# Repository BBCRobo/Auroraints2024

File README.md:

Here is a repository of all our hardware (structural) parts, this only includes unique parts

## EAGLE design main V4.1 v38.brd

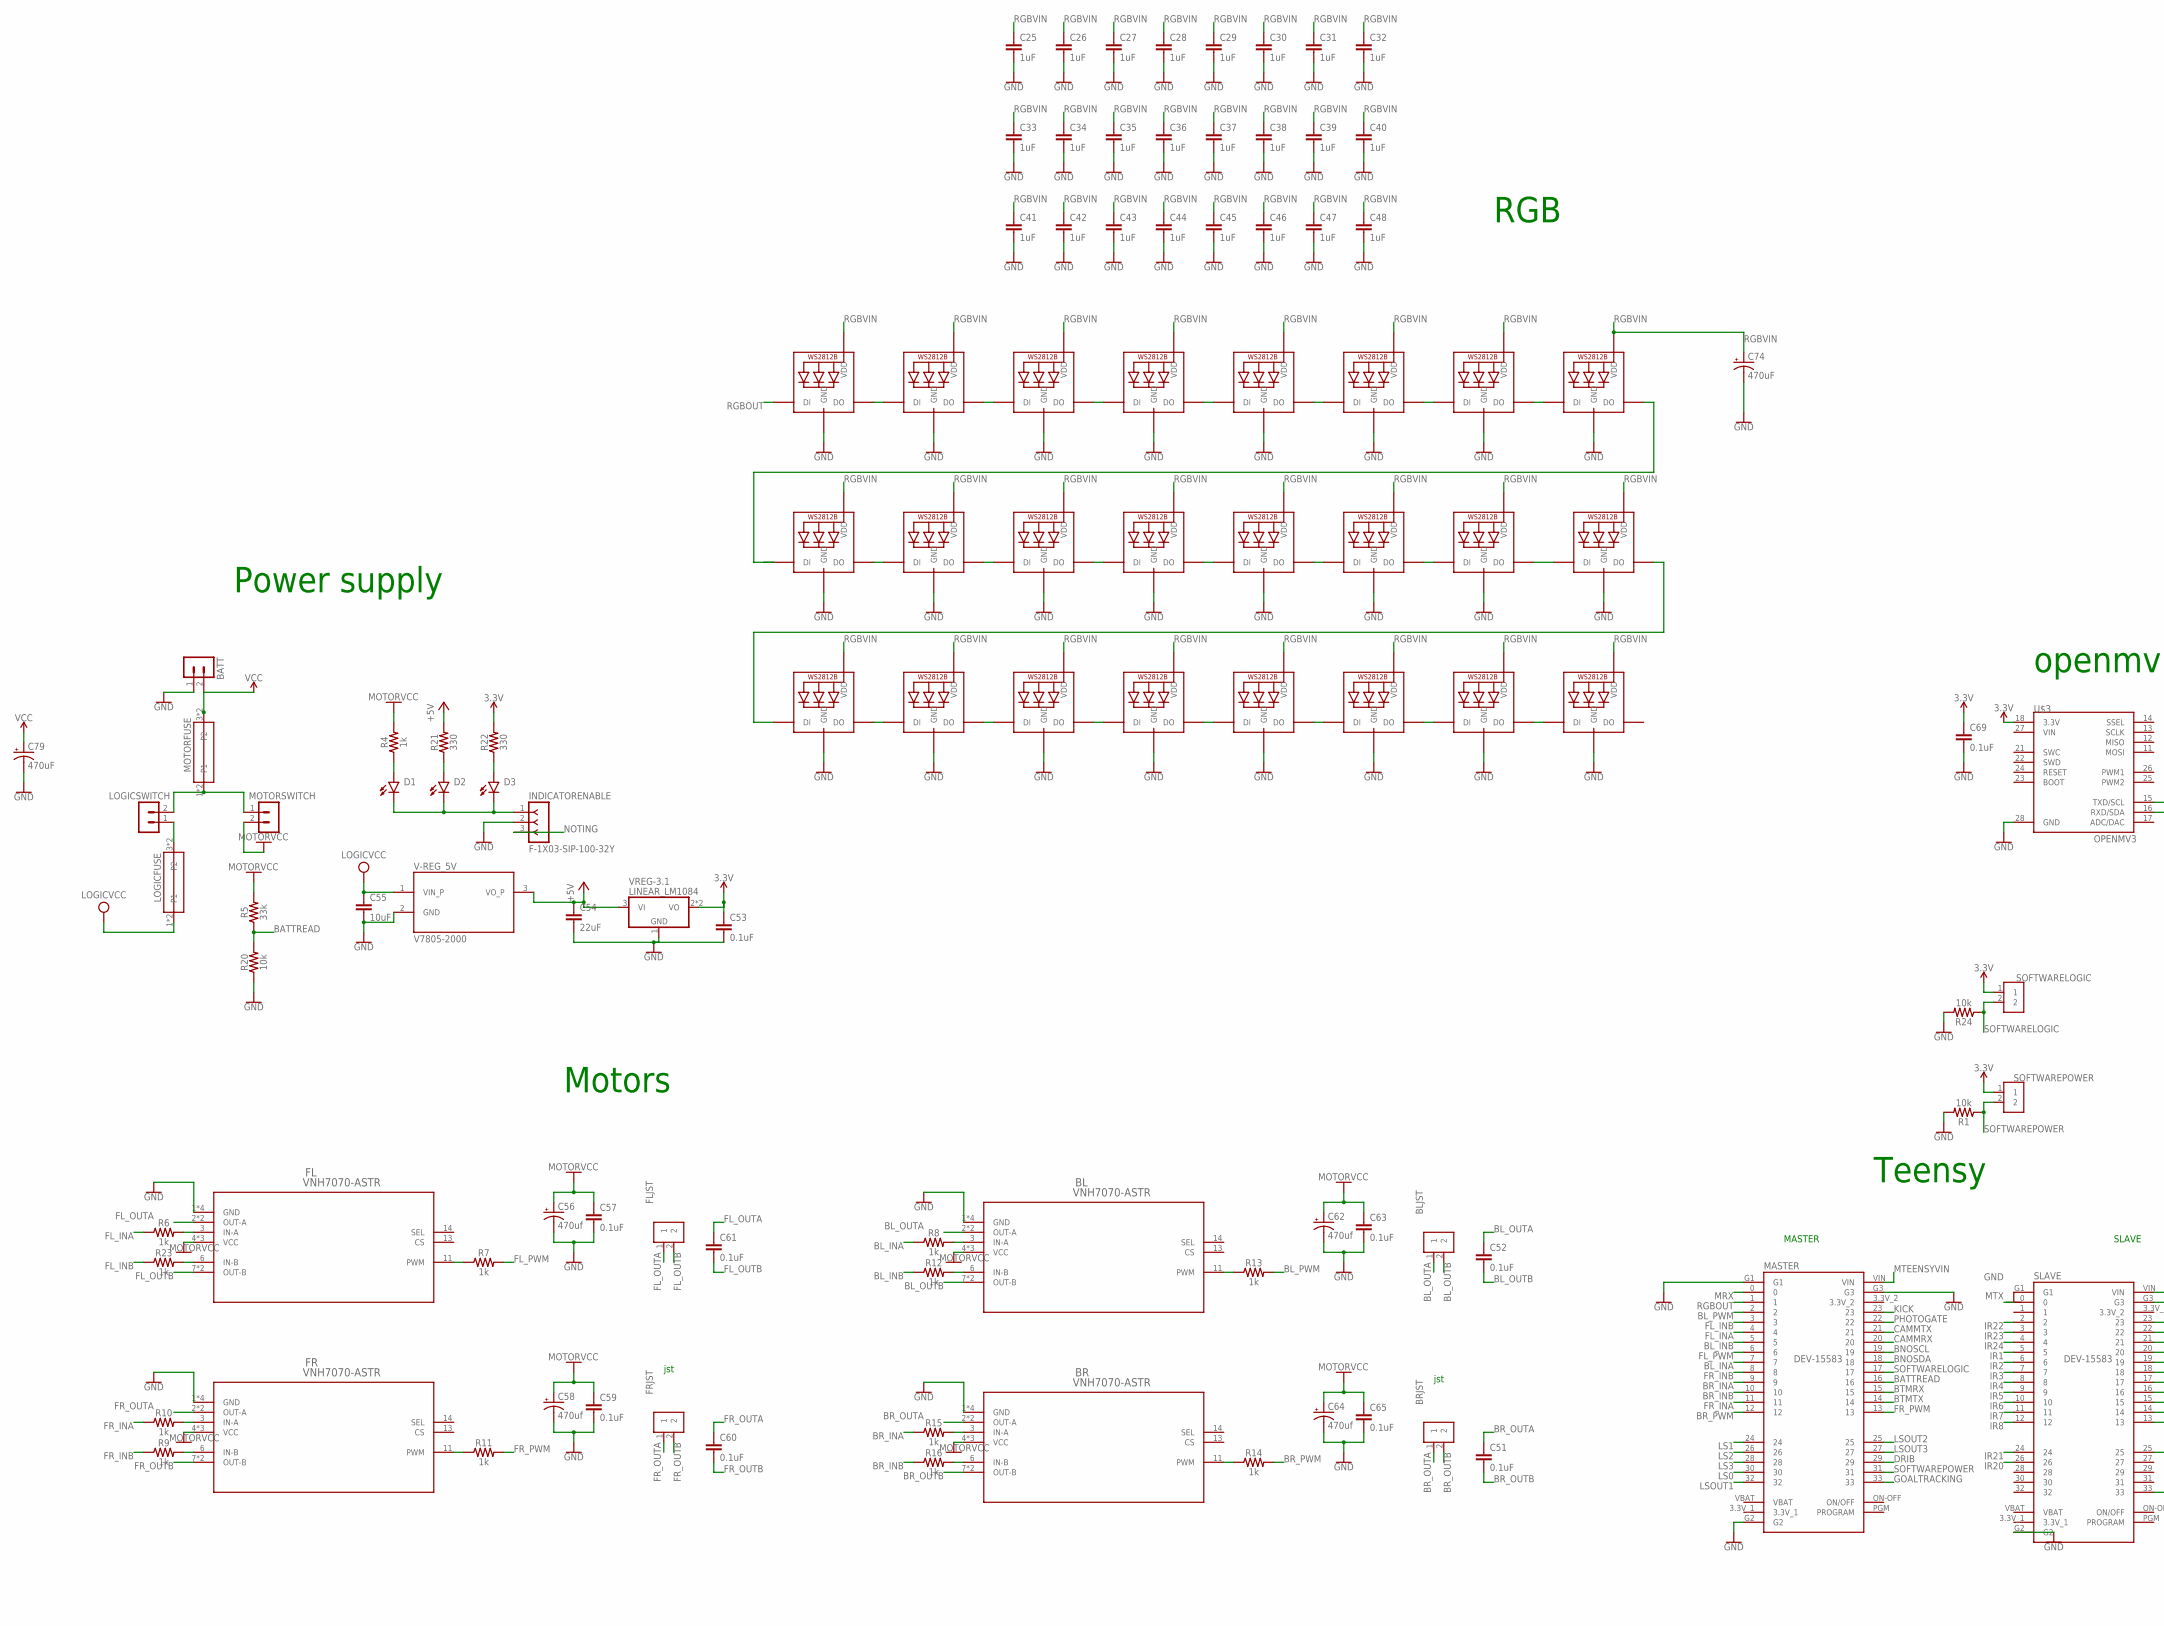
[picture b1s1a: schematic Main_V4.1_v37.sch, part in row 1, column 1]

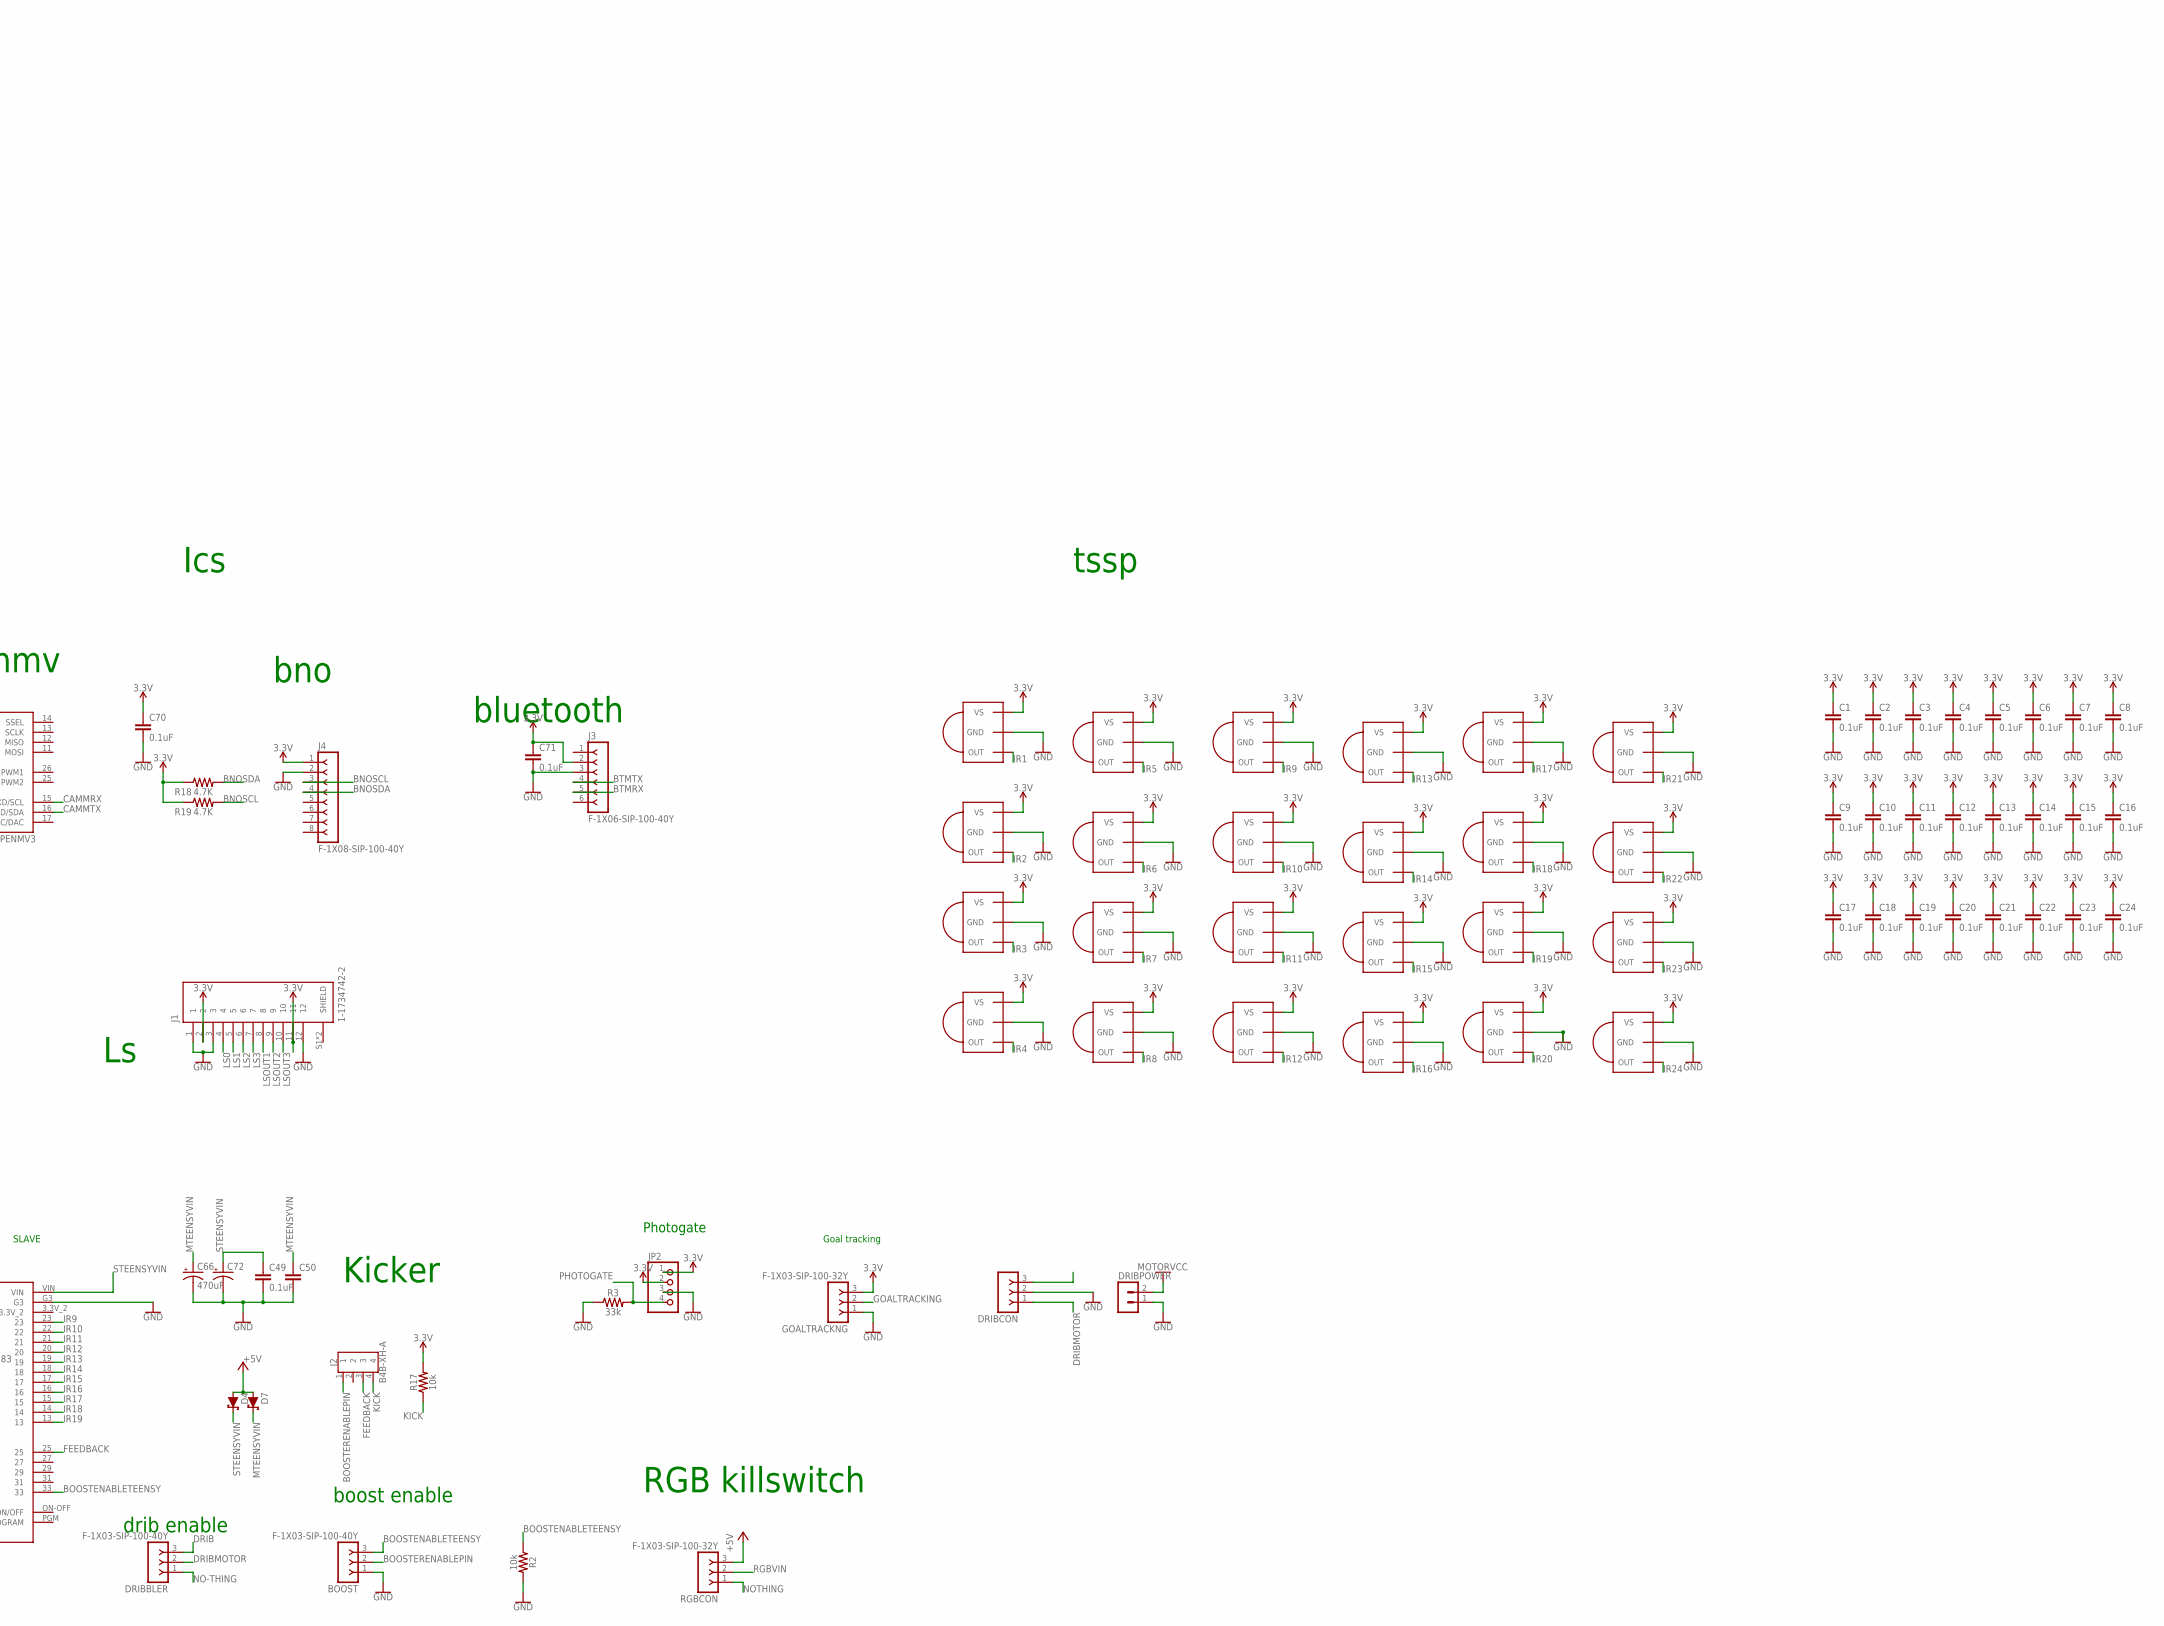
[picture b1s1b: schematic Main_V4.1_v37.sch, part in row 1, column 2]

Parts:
BATT: B2P-VH-B; B2P-VH
BL: VNH7070-ASTR
BLJST: B2B-XH-A
BOOST: F-1X03-SIP-100-40Y; SIP-100-03-40Y
BR: VNH7070-ASTR
BRJST: B2B-XH-A
C1, C2, C3, C4, C5, C6, C7, C8, C9, C10, C11, C12, C13, C14, C15, C16, C17, C18, C19, C20, C21, C22, C23, C24, C49, C50, C51, C52, C53, C57, C59, C60, C61, C63, C65, C69, C70, C71: 0.1uF; 0603
C25, C26, C27, C28, C29, C30, C31, C32, C33, C34, C35, C36, C37, C38, C39, C40, C41, C42, C43, C44, C45, C46, C47, C48: 1uF; 0603
C54: 22uF; 0603
C55: 10uF; 0603
C56, C58, C62, C64: 470uf; CPOL-RADIAL-5MM-10MM-KIT
C66, C72, C74, C79: 470uF; CPOL-RADIAL-5MM-10MM-KIT
D1, D2, D3: CHIP-FLAT-Y_0603-0.55MM; LEDC1608X55N_FLAT-Y
D4, D7: 1A/40V/500mV; SMA-DIODE
DRIBBLER: F-1X03-SIP-100-40Y; SIP-100-03-40Y
DRIBCON: F-1X03-SIP-100-32Y; SIP-100-03-32Y
DRIBPOWER: B2P-VH-B; B2P-VH
FL: VNH7070-ASTR
FLJST: B2B-XH-A
FR: VNH7070-ASTR
FRJST: B2B-XH-A
GOALTRACKNG: F-1X03-SIP-100-32Y; SIP-100-03-32Y
INDICATORENABLE: F-1X03-SIP-100-32Y; SIP-100-03-32Y
IR1, IR2, IR3, IR4, IR5, IR6, IR7, IR8, IR9, IR10, IR11, IR12, IR13, IR14, IR15, IR16, IR17, IR18, IR19, IR20, IR21, IR22, IR23, IR24: TSSP58038; MINICAST
J1: 1-1734742-2; TE_1-1734742-2
J2: B4B-XH-A
J3: F-1X06-SIP-100-40Y; SIP-100-06-40Y
J4: F-1X08-SIP-100-40Y; SIP-100-08-40Y
JP2: PINHD-1X4; 1X04
LED1, LED2, LED3, LED4, LED5, LED6, LED7, LED8, LED9, LED10, LED11, LED12, LED13, LED14, LED15, LED16, LED17, LED18, LED19, LED20, LED21, LED22, LED23, LED24: WS2812B_5050N; WS2812B-NARROW
LOGICFUSE: 3568-FUSEHOLDER
LOGICSWITCH: B2P-VH-B; B2P-VH
MASTER: DEV-15583; MODULE_DEV-15583
MOTORFUSE: 3568-FUSEHOLDER
MOTORSWITCH: B2P-VH-B; B2P-VH
R1, R2, R17, R20, R24: 10k; 0603
R3, R5: 33k; 0603
R4, R6, R7, R8, R9, R10, R11, R12, R13, R14, R15, R16, R23: 1k; 0603
R18, R19: 4.7K; 0603
R21, R22: 330; 0603
RGBCON: F-1X03-SIP-100-32Y; SIP-100-03-32Y
SLAVE: DEV-15583; MODULE_DEV-15583
SOFTWARELOGIC: B2B-XH-A
SOFTWAREPOWER: B2B-XH-A
U$3: OPENMV3
V-REG_5V: V7805-2000; CONV_V7805-2000
VREG-3.1: LINEAR_LM1084; LINEAR_TO263-3

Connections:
3.3V: C1.1, C2.1, C3.1, C4.1, C5.1, C6.1, C7.1, C8.1, C9.1, C10.1, C11.1, C12.1, C13.1, C14.1, C15.1, C16.1, C17.1, C18.1, C19.1, C20.1, C21.1, C22.1, C23.1, C24.1, C53.1, C69.1, C70.1, C71.1, GOALTRACKNG.3, IR1.3 (VS), IR2.3 (VS), IR3.3 (VS), IR4.3 (VS), IR5.3 (VS), IR6.3 (VS), IR7.3 (VS), IR8.3 (VS), IR9.3 (VS), IR10.3 (VS), IR11.3 (VS), IR12.3 (VS), IR13.3 (VS), IR14.3 (VS), IR15.3 (VS), IR16.3 (VS), IR17.3 (VS), IR18.3 (VS), IR19.3 (VS), IR20.3 (VS), IR21.3 (VS), IR22.3 (VS), IR23.3 (VS), IR24.3 (VS), J1.2, J1.11, J3.2, J4.1, JP2.1, JP2.2, R17.2, R18.1, R19.1, R22.2, SOFTWARELOGIC.1, SOFTWAREPOWER.1, U$3.18 (3.3V), VREG-3.1.2 (VO), VREG-3.1.TAB (VO)
3.3V_1: MASTER.3.3V_1, SLAVE.3.3V_1
3.3V_2: MASTER.3.3V_2, SLAVE.3.3V_2
+5V: C54.1, D4.A, D7.A, R21.2, RGBCON.3, V-REG_5V.3 (VO_P), VREG-3.1.3 (VI)
BATTREAD: MASTER.16, R5.1, R20.2
BL_INA: MASTER.7, R8.1
BL_INB: MASTER.5, R12.1
BL_OUTA: BL.2 (OUT-A), BL.15 (OUT-A), BLJST.1, C52.1
BL_OUTB: BL.7 (OUT-B), BL.10 (OUT-B), BLJST.2, C52.2
BL_PWM: MASTER.2, R13.2
BNOSCL: J4.3, MASTER.19, R19.2
BNOSDA: J4.4, MASTER.18, R18.2
BOOSTENABLETEENSY: BOOST.3, R2.1, SLAVE.33
BOOSTERENABLEPIN: BOOST.2, J2.1
BR_INA: MASTER.9, R15.1
BR_INB: MASTER.10, R16.1
BR_OUTA: BR.2 (OUT-A), BR.15 (OUT-A), BRJST.1, C51.1
BR_OUTB: BR.7 (OUT-B), BR.10 (OUT-B), BRJST.2, C51.2
BR_PWM: MASTER.12, R14.2
BTMRX: J3.5, MASTER.15
BTMTX: J3.4, MASTER.14
CAMMRX: MASTER.20, U$3.15 (TXD/SCL)
CAMMTX: MASTER.21, U$3.16 (RXD/SDA)
DRIB: DRIBBLER.3, MASTER.29
DRIBMOTOR: DRIBBLER.2, DRIBCON.1
FEEDBACK: J2.3, SLAVE.25
FL_INA: MASTER.4, R6.1
FL_INB: MASTER.3, R23.1
FL_OUTA: C61.1, FL.2 (OUT-A), FL.15 (OUT-A), FLJST.1
FL_OUTB: C61.2, FL.7 (OUT-B), FL.10 (OUT-B), FLJST.2
FL_PWM: MASTER.6, R7.2
FR_INA: MASTER.11, R10.1
FR_INB: MASTER.8, R9.1
FR_OUTA: C60.1, FR.2 (OUT-A), FR.15 (OUT-A), FRJST.1
FR_OUTB: C60.2, FR.7 (OUT-B), FR.10 (OUT-B), FRJST.2
FR_PWM: MASTER.13, R11.2
GND: BATT.1, BL.1 (GND), BL.8 (GND), BL.9 (GND), BL.16 (GND), BOOST.1, BR.1 (GND), BR.8 (GND), BR.9 (GND), BR.16 (GND), C1.2, C2.2, C3.2, C4.2, C5.2, C6.2, C7.2, C8.2, C9.2, C10.2, C11.2, C12.2, C13.2, C14.2, C15.2, C16.2, C17.2, C18.2, C19.2, C20.2, C21.2, C22.2, C23.2, C24.2, C25.2, C26.2, C27.2, C28.2, C29.2, C30.2, C31.2, C32.2, C33.2, C34.2, C35.2, C36.2, C37.2, C38.2, C39.2, C40.2, C41.2, C42.2, C43.2, C44.2, C45.2, C46.2, C47.2, C48.2, C49.2, C50.2, C53.2, C54.2, C55.2, C56.-, C57.2, C58.-, C59.2, C62.-, C63.2, C64.-, C65.2, C66.-, C69.2, C70.2, C71.2, C72.-, C74.-, C79.-, DRIBCON.2, DRIBPOWER.1, FL.1 (GND), FL.8 (GND), FL.9 (GND), FL.16 (GND), FR.1 (GND), FR.8 (GND), FR.9 (GND), FR.16 (GND), GOALTRACKNG.1, INDICATORENABLE.2, IR1.2 (GND), IR2.2 (GND), IR3.2 (GND), IR4.2 (GND), IR5.2 (GND), IR6.2 (GND), IR7.2 (GND), IR8.2 (GND), IR9.2 (GND), IR10.2 (GND), IR11.2 (GND), IR12.2 (GND), IR13.2 (GND), IR14.2 (GND), IR15.2 (GND), IR16.2 (GND), IR17.2 (GND), IR18.2 (GND), IR19.2 (GND), IR20.2 (GND), IR21.2 (GND), IR22.2 (GND), IR23.2 (GND), IR24.2 (GND), J1.1, J1.3, J1.12, J3.3, J4.2, JP2.3, LED1.3-GND (GND), LED2.3-GND (GND), LED3.3-GND (GND), LED4.3-GND (GND), LED5.3-GND (GND), LED6.3-GND (GND), LED7.3-GND (GND), LED8.3-GND (GND), LED9.3-GND (GND), LED10.3-GND (GND), LED11.3-GND (GND), LED12.3-GND (GND), LED13.3-GND (GND), LED14.3-GND (GND), LED15.3-GND (GND), LED16.3-GND (GND), LED17.3-GND (GND), LED18.3-GND (GND), LED19.3-GND (GND), LED20.3-GND (GND), LED21.3-GND (GND), LED22.3-GND (GND), LED23.3-GND (GND), LED24.3-GND (GND), MASTER.G1, MASTER.G2, MASTER.G3, R1.2, R2.2, R3.1, R20.1, R24.2, SLAVE.G1, SLAVE.G2, SLAVE.G3, U$3.28 (GND), V-REG_5V.2 (GND), VREG-3.1.1 (GND)
GOALTRACKING: GOALTRACKNG.2, MASTER.33
IR1: IR1.1 (OUT), SLAVE.5
IR2: IR2.1 (OUT), SLAVE.6
IR3: IR3.1 (OUT), SLAVE.7
IR4: IR4.1 (OUT), SLAVE.8
IR5: IR5.1 (OUT), SLAVE.9
IR6: IR6.1 (OUT), SLAVE.10
IR7: IR7.1 (OUT), SLAVE.11
IR8: IR8.1 (OUT), SLAVE.12
IR9: IR9.1 (OUT), SLAVE.23
IR10: IR10.1 (OUT), SLAVE.22
IR11: IR11.1 (OUT), SLAVE.21
IR12: IR12.1 (OUT), SLAVE.20
IR13: IR13.1 (OUT), SLAVE.19
IR14: IR14.1 (OUT), SLAVE.18
IR15: IR15.1 (OUT), SLAVE.17
IR16: IR16.1 (OUT), SLAVE.16
IR17: IR17.1 (OUT), SLAVE.15
IR18: IR18.1 (OUT), SLAVE.14
IR19: IR19.1 (OUT), SLAVE.13
IR20: IR20.1 (OUT), SLAVE.26
IR21: IR21.1 (OUT), SLAVE.24
IR22: IR22.1 (OUT), SLAVE.2
IR23: IR23.1 (OUT), SLAVE.3
IR24: IR24.1 (OUT), SLAVE.4
KICK: J2.4, MASTER.23, R17.1
LOGICVCC: C55.1, LOGICFUSE.1, LOGICFUSE.2 (P1), V-REG_5V.1 (VIN_P)
LS0: J1.4, MASTER.30
LS1: J1.5, MASTER.24
LS2: J1.6, MASTER.26
LS3: J1.7, MASTER.28
LSOUT1: J1.8, MASTER.32
LSOUT2: J1.9, MASTER.25
LSOUT3: J1.10, MASTER.27
MOTORVCC: BL.4 (VCC), BL.5 (VCC), BL.12 (VCC), BR.4 (VCC), BR.5 (VCC), BR.12 (VCC), C56.+, C57.1, C58.+, C59.1, C62.+, C63.1, C64.+, C65.1, DRIBPOWER.2, FL.4 (VCC), FL.5 (VCC), FL.12 (VCC), FR.4 (VCC), FR.5 (VCC), FR.12 (VCC), MOTORSWITCH.2, R4.2, R5.2
MRX: MASTER.0
MTEENSYVIN: C50.1, C66.+, D7.C, MASTER.VIN
MTX: SLAVE.0
unnamed: LOGICSWITCH.2, MOTORFUSE.1, MOTORFUSE.2 (P1), MOTORSWITCH.1
unnamed: D1.C, D2.C, D3.C, INDICATORENABLE.1
unnamed: FL.3 (IN-A), R6.2
unnamed: D1.A, R4.1
unnamed: LOGICFUSE.3 (P2), LOGICFUSE.4 (P2), LOGICSWITCH.1
unnamed: D2.A, R21.1
unnamed: FL.6 (IN-B), R23.2
unnamed: FL.11 (PWM), R7.1
unnamed: FR.3 (IN-A), R10.2
unnamed: FR.11 (PWM), R11.1
unnamed: FR.6 (IN-B), R9.2
unnamed: BL.3 (IN-A), R8.2
unnamed: BL.11 (PWM), R13.1
unnamed: BL.6 (IN-B), R12.2
unnamed: BR.3 (IN-A), R15.2
unnamed: BR.11 (PWM), R14.1
unnamed: BR.6 (IN-B), R16.2
unnamed: D3.A, R22.1
unnamed: LED19.2-DOUT (DO), LED20.4-DIN (DI)
unnamed: LED23.2-DOUT (DO), LED24.4-DIN (DI)
unnamed: LED22.2-DOUT (DO), LED23.4-DIN (DI)
unnamed: LED21.2-DOUT (DO), LED22.4-DIN (DI)
unnamed: LED18.2-DOUT (DO), LED19.4-DIN (DI)
unnamed: LED15.2-DOUT (DO), LED16.4-DIN (DI)
unnamed: LED3.2-DOUT (DO), LED4.4-DIN (DI)
unnamed: LED9.2-DOUT (DO), LED10.4-DIN (DI)
unnamed: LED10.2-DOUT (DO), LED11.4-DIN (DI)
unnamed: LED12.2-DOUT (DO), LED13.4-DIN (DI)
unnamed: LED13.2-DOUT (DO), LED14.4-DIN (DI)
unnamed: LED14.2-DOUT (DO), LED15.4-DIN (DI)
unnamed: LED6.2-DOUT (DO), LED7.4-DIN (DI)
unnamed: LED8.2-DOUT (DO), LED9.4-DIN (DI)
unnamed: LED16.2-DOUT (DO), LED17.4-DIN (DI)
unnamed: LED5.2-DOUT (DO), LED6.4-DIN (DI)
unnamed: LED4.2-DOUT (DO), LED5.4-DIN (DI)
unnamed: LED2.2-DOUT (DO), LED3.4-DIN (DI)
unnamed: LED1.2-DOUT (DO), LED2.4-DIN (DI)
unnamed: LED11.2-DOUT (DO), LED12.4-DIN (DI)
unnamed: LED7.2-DOUT (DO), LED8.4-DIN (DI)
unnamed: LED17.2-DOUT (DO), LED18.4-DIN (DI)
unnamed: LED20.2-DOUT (DO), LED21.4-DIN (DI)
NO-THING: DRIBBLER.1
NOTHING: RGBCON.1
NOTING: INDICATORENABLE.3
PHOTOGATE: JP2.4, MASTER.22, R3.2
RGBOUT: LED1.4-DIN (DI), MASTER.1
RGBVIN: C25.1, C26.1, C27.1, C28.1, C29.1, C30.1, C31.1, C32.1, C33.1, C34.1, C35.1, C36.1, C37.1, C38.1, C39.1, C40.1, C41.1, C42.1, C43.1, C44.1, C45.1, C46.1, C47.1, C48.1, C74.+, LED1.1-VDD (VDD), LED2.1-VDD (VDD), LED3.1-VDD (VDD), LED4.1-VDD (VDD), LED5.1-VDD (VDD), LED6.1-VDD (VDD), LED7.1-VDD (VDD), LED8.1-VDD (VDD), LED9.1-VDD (VDD), LED10.1-VDD (VDD), LED11.1-VDD (VDD), LED12.1-VDD (VDD), LED13.1-VDD (VDD), LED14.1-VDD (VDD), LED15.1-VDD (VDD), LED16.1-VDD (VDD), LED17.1-VDD (VDD), LED18.1-VDD (VDD), LED19.1-VDD (VDD), LED20.1-VDD (VDD), LED21.1-VDD (VDD), LED22.1-VDD (VDD), LED23.1-VDD (VDD), LED24.1-VDD (VDD), RGBCON.2
SOFTWARELOGIC: MASTER.17, R24.1, SOFTWARELOGIC.2
SOFTWAREPOWER: MASTER.31, R1.1, SOFTWAREPOWER.2
STEENSYVIN: C49.1, C72.+, D4.C, SLAVE.VIN
VBAT: MASTER.VBAT, SLAVE.VBAT
VCC: BATT.2, C79.+, MOTORFUSE.3 (P2), MOTORFUSE.4 (P2)
VIN: U$3.27 (VIN)

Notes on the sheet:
jst
Power supply
Motors
bluetooth
bno
openmv
Ics
Teensy
Photogate
MASTER
SLAVE
tssp
Kicker
RGB
RGB killswitch
Goal tracking
boost enable
drib enable

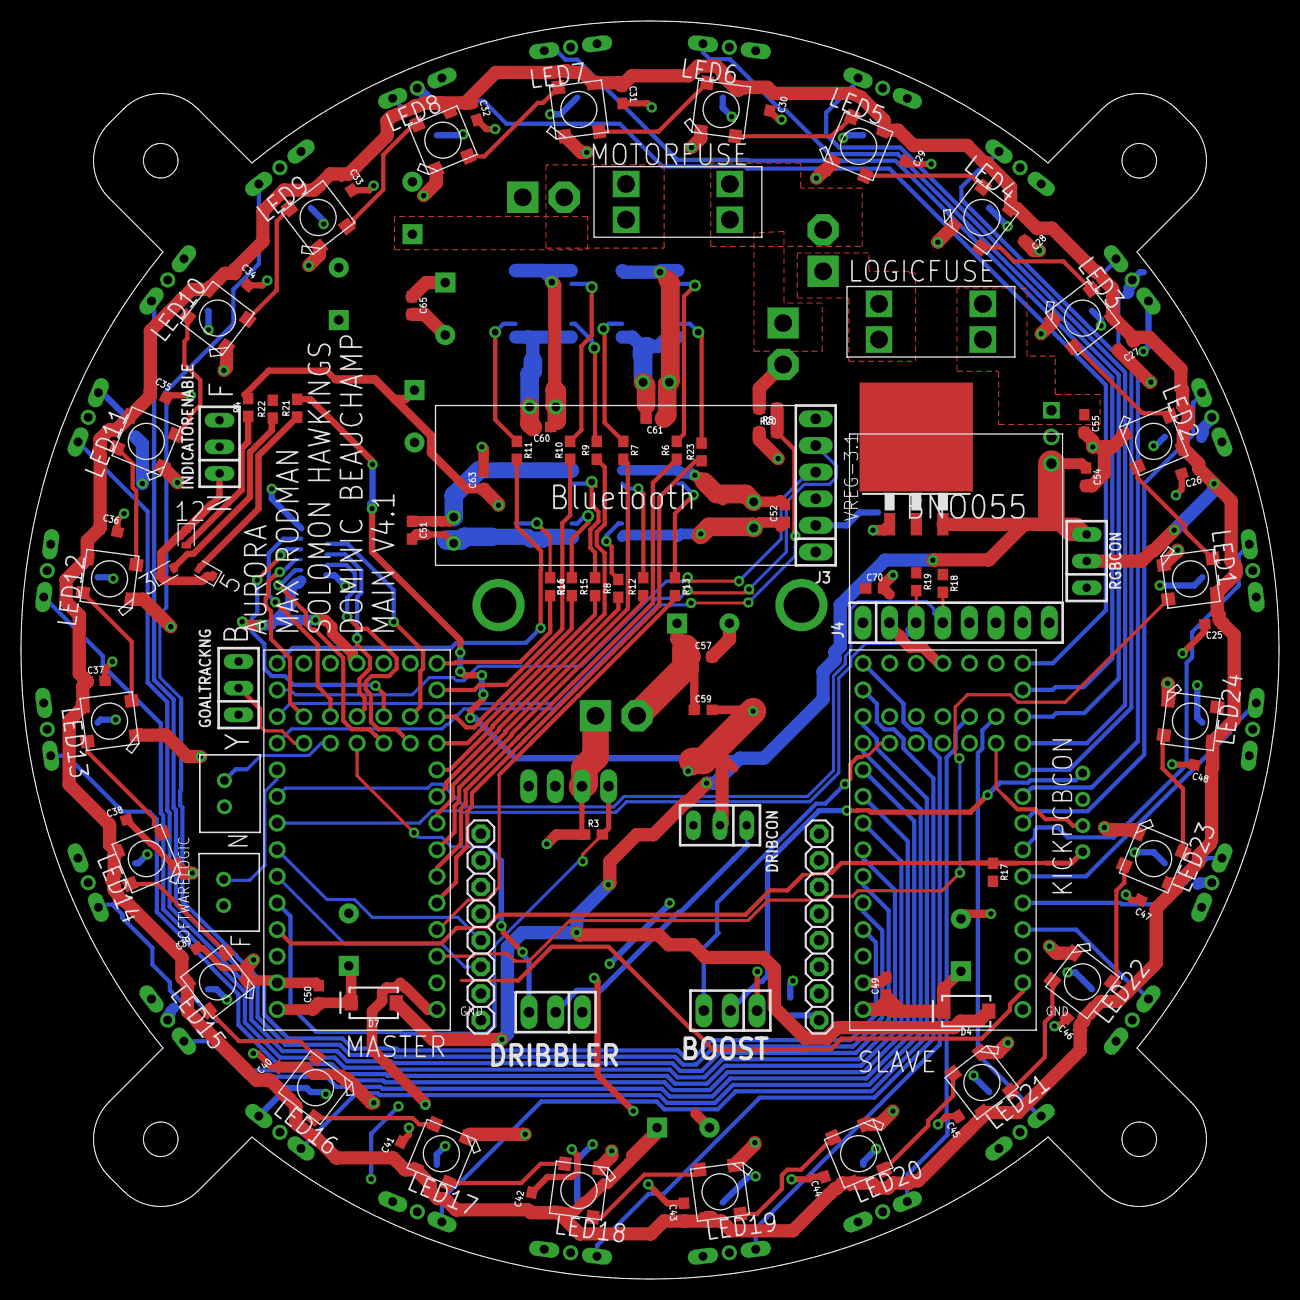
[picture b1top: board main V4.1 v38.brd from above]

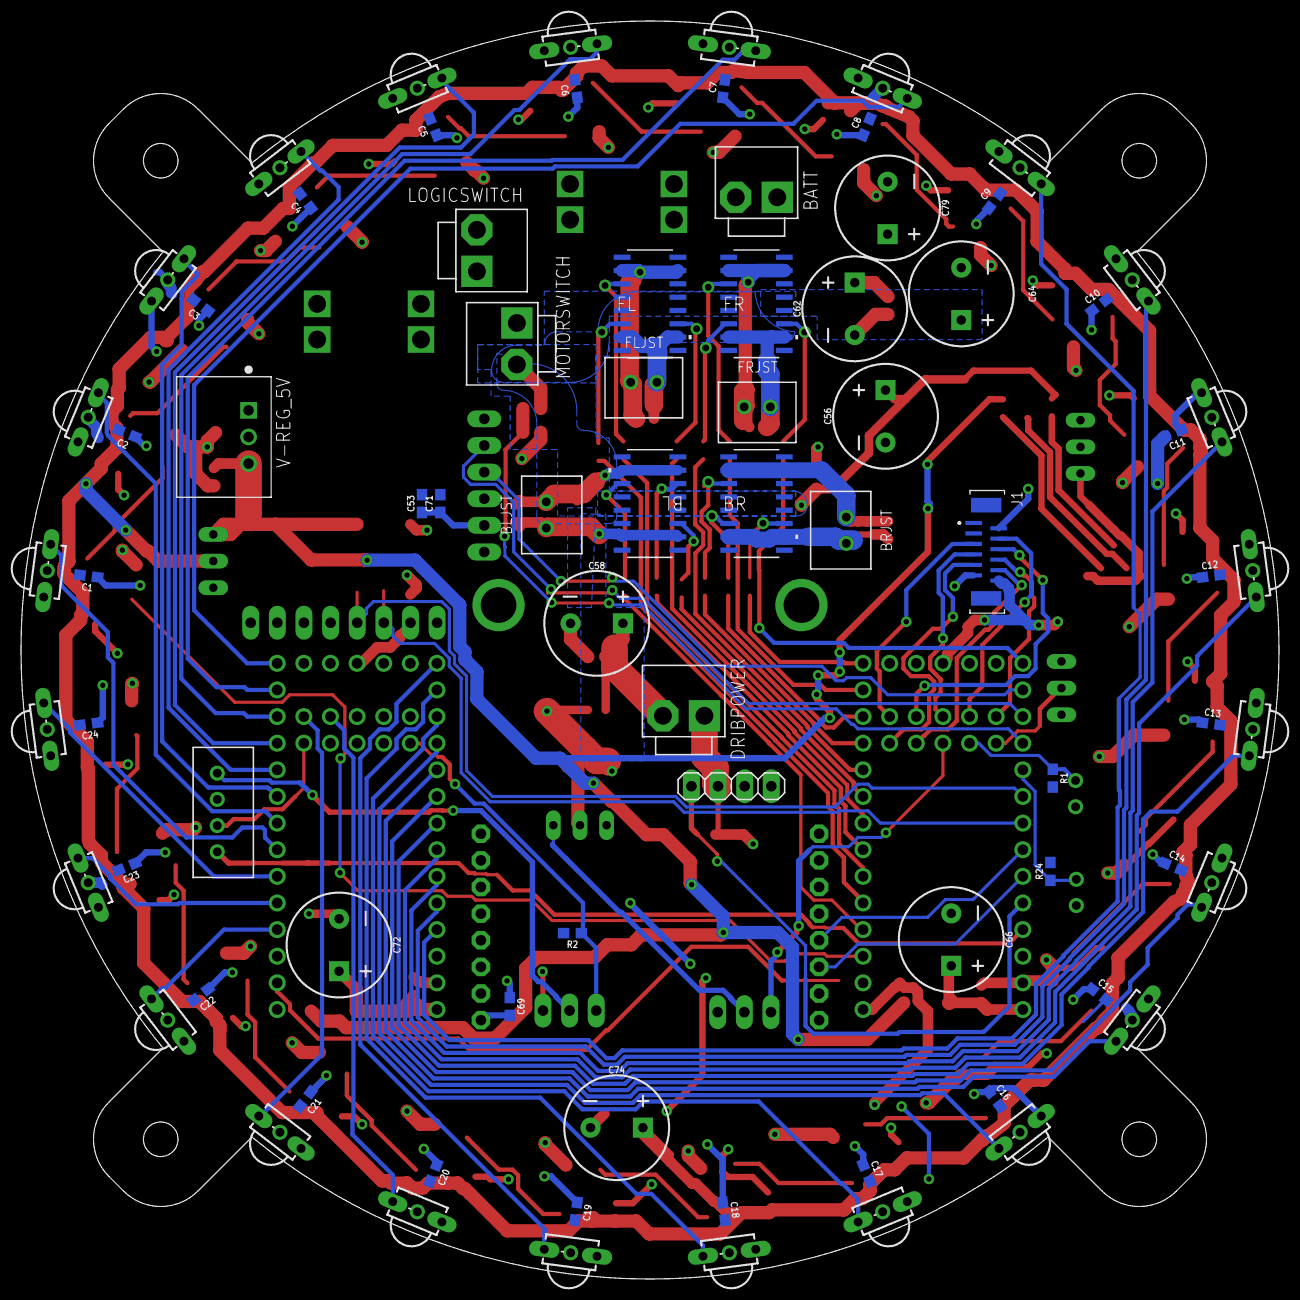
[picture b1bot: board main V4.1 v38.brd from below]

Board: 2 copper layers, 120.0 x 120.0 mm, 181 parts (78 on the bottom side), 122 nets.

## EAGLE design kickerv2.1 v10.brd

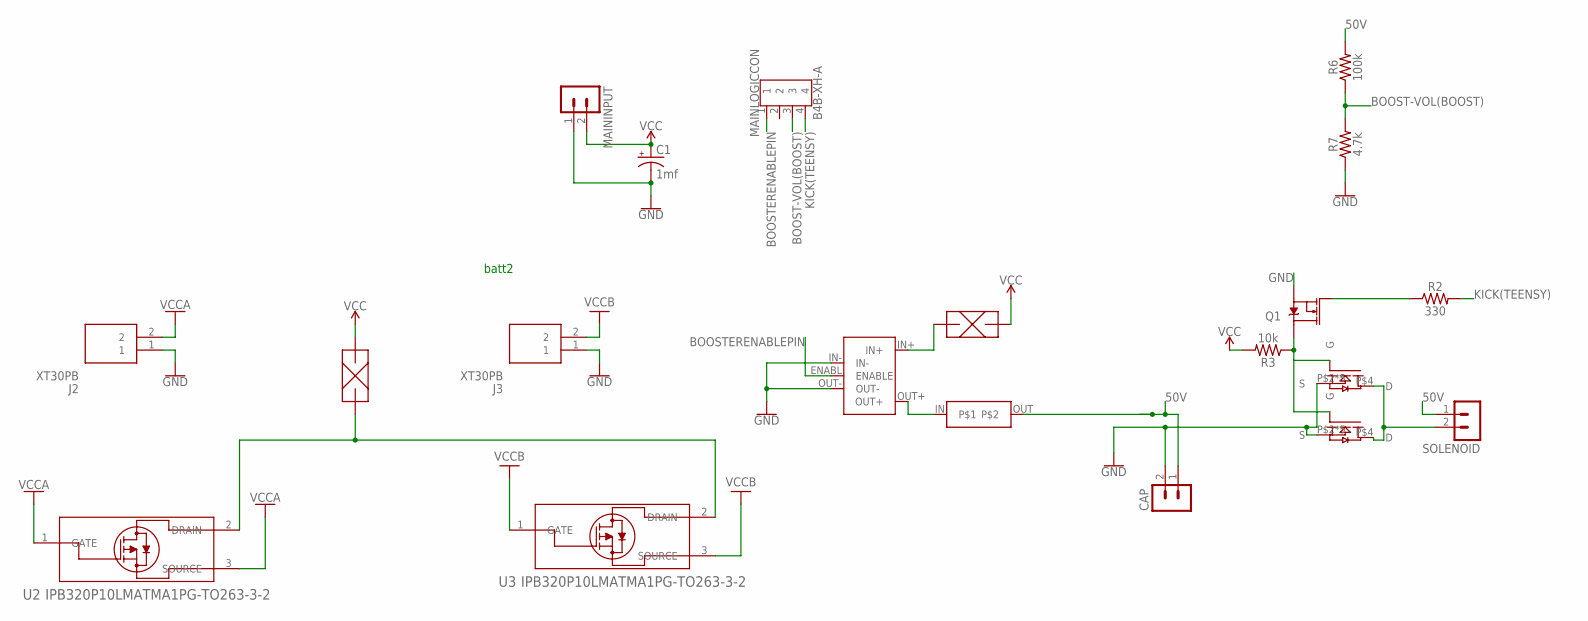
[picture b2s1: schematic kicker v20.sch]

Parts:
C1: 1mf; CPOL-RADIAL-5MM-10MM-KIT
CAP: B2P-VH-FB-B
J2, J3: XT30PB
MAININPUT: B2P-VH-B; B2P-VH
MAINLOGICCON: B4B-XH-A
Q1: 5.8A/30V/35mΩ; SOT23-3
R2: 330; 0603
R3: 10k; 0603
R6: 100k; 0603
R7: 4.7k; 0603
SOLENOID: B2P-VH-FB-B
U2, U3: IPB320P10LMATMA1PG-TO263-3-2; PG-TO263-3-2
U$1, U$2: N-CH_D2PAK-7P; D2PAK-7P
U$3: HPRE
U$4: VOLTAGEBOOSTER
U$5, U$6: FUSE-HORIZONTAL; MINI-RIGHT

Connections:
50V: CAP.1, R6.2, SOLENOID.1, U$3.OUT
BOOST-VOL(BOOST): MAINLOGICCON.3, R6.1, R7.2
BOOSTERENABLEPIN: MAINLOGICCON.1, U$4.ENABL (ENABLE)
GND: C1.-, CAP.2, J2.1, J3.1, MAININPUT.1, Q1.2 (S), R7.1, U$1.P$2 (S), U$1.P$3 (S), U$1.P$5 (S), U$1.P$6 (S), U$1.P$7 (S), U$2.P$2 (S), U$2.P$3 (S), U$2.P$5 (S), U$2.P$6 (S), U$2.P$7 (S), U$4.IN-, U$4.OUT-
KICK(TEENSY): MAINLOGICCON.4, R2.2
unnamed: SOLENOID.2, U$1.P$4 (D), U$2.P$4 (D)
unnamed: U$4.IN+, U$5.P$1, U$5.P$3
unnamed: U$3.IN, U$4.OUT+
unnamed: Q1.3 (D), R3.1, U$1.P$1 (G), U$2.P$1 (G)
unnamed: Q1.1 (G), R2.1
unnamed: U2.2 (DRAIN), U3.2 (DRAIN), U$6.P$1, U$6.P$3
VCC: C1.+, MAININPUT.2, R3.2, U$5.P$2, U$5.P$4, U$6.P$2, U$6.P$4
VCCA: J2.2, U2.1 (GATE), U2.3 (SOURCE)
VCCB: J3.2, U3.1 (GATE), U3.3 (SOURCE)

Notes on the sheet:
batt2

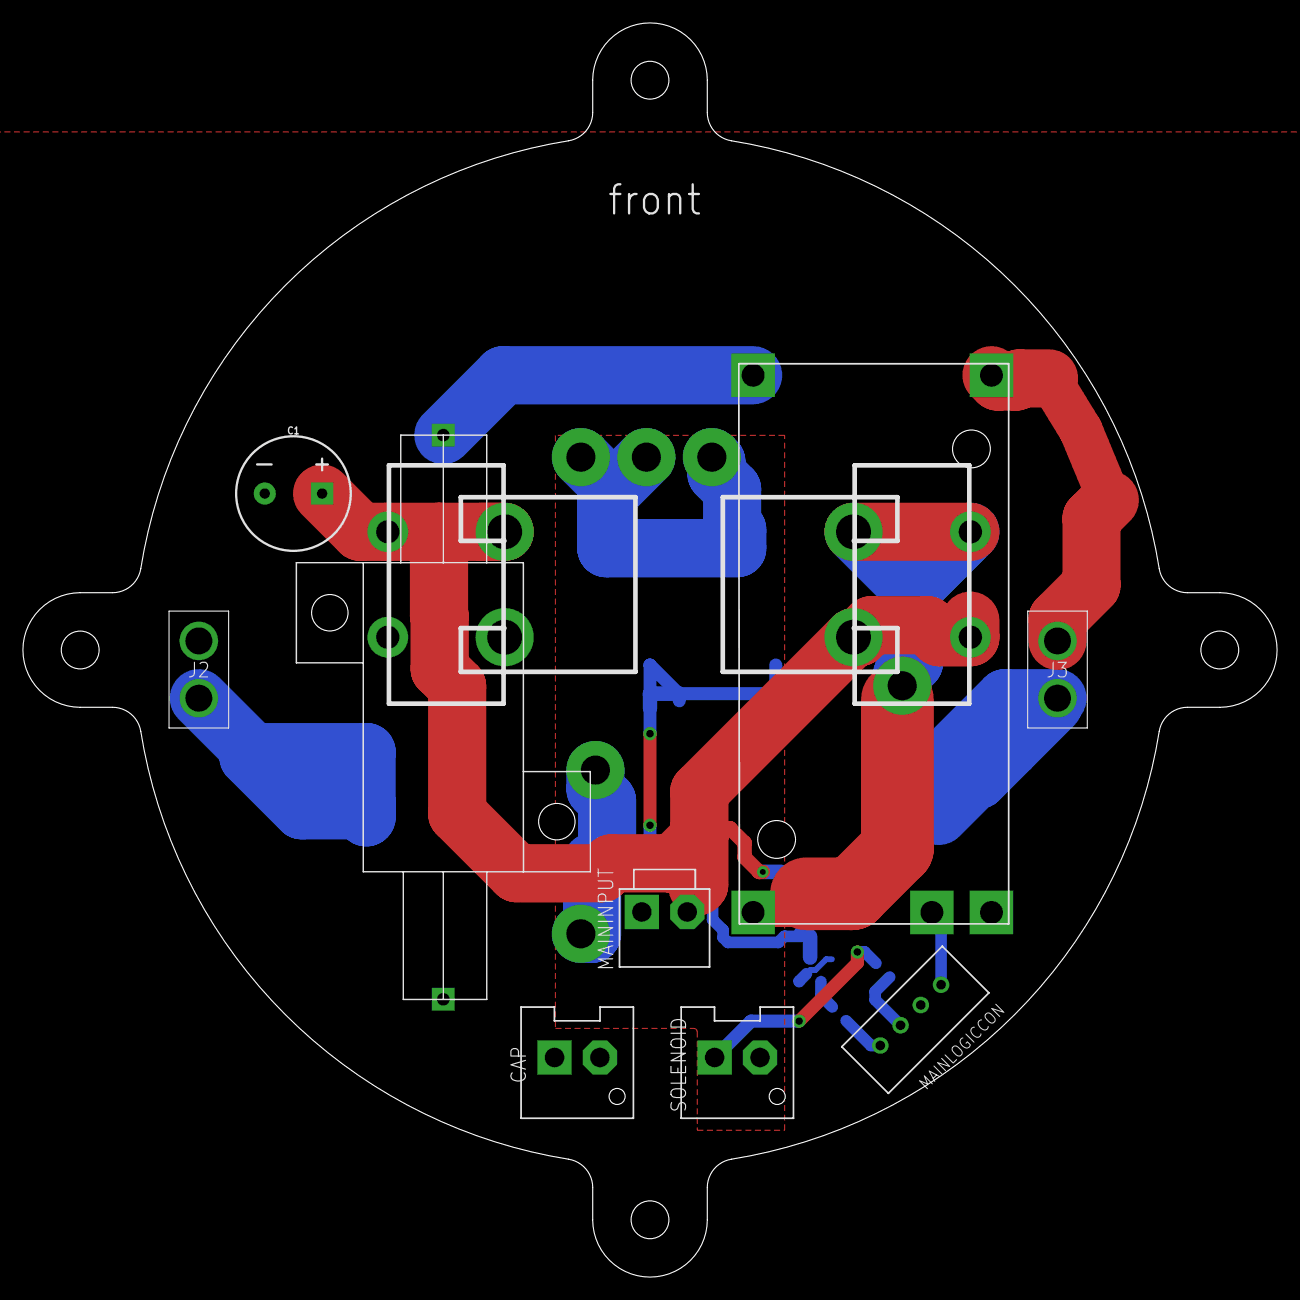
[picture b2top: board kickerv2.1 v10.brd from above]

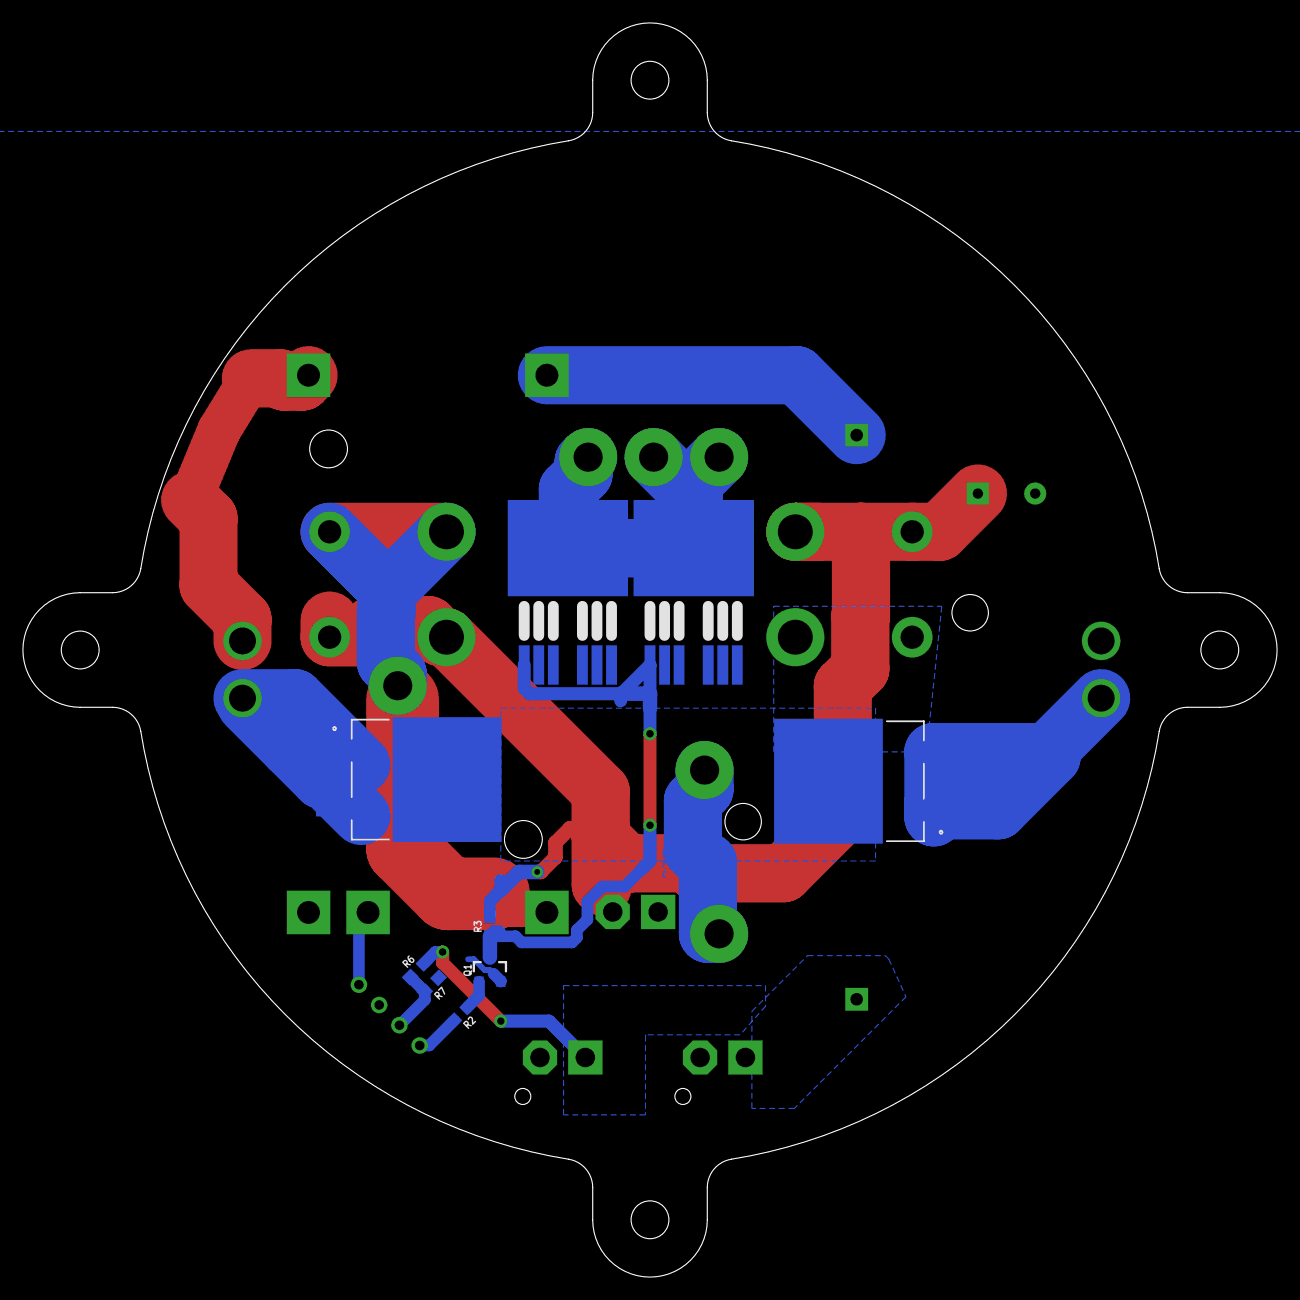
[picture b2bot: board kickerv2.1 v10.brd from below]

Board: 2 copper layers, 109.4 x 109.4 mm, 20 parts (9 on the bottom side), 14 nets.

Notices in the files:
parts and their libraries:
SparkFun-Resistors: Licensing: Creative Commons ShareAlike 4.0 International - https://creativecommons.org/licenses/by-sa/4.0
COPYRIGHT: Copyright (C) 2022 Ultra Librarian. All rights reserved.
con-headers-jp: Copyright (C) 2008, Bob Starr
